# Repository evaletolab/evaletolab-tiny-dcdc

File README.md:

# Low cost, high efficiency, step-up DC-DC converter  
> [ input min 0.7V or 0.85V - output 3V, 3.3V or 5V - boost efficiency max 95% ]

This is an easy and tiny way to manage variable and small input voltage with your MCU project.
Using the [LTC3525](http://www.linear.com/product/LTC3525) you always get constant output voltage whatever your input voltage. Even at 1.2V as input the step-up keep >85% of the energy.

* **Up to 95% Efficiency**
* **Ultra small case 6x11mm**
* External solar panel input **with diode protection**
* Input startup voltage at 0.7V or 0.85V
* Plug external small battery or a super capacitor
* Output Disconnect and Inrush Current Limit
* Fixed Output Voltages of 3V, 3.3V or 5V
* Delivers 65mA at 3V from a 1V Input
* Delivers 60mA at 3.3V from a 1V Input, or 140mA at 3.3V from a 1.8V Input
* Delivers 175mA at 5V from a 3V Input
* <1μA Shutdown Current

<!--  -->

# The PCB

**THIS IS ALPHA SOFTWARE/HARDWARE AND SHOULD BE TREATED ACCORDINGLY.**
**IT IS FUN TO GET RUNNING, BUT EXPECT THINGS TO BE BROKEN.**
 
## License
GPL3
> Copyright (c) 2012 Olivier Evalet (http://evaletolab.ch/)

Permission is hereby granted, free of charge, to any person obtaining a copy
of this software and associated documentation files (the “Software”), to deal
in the Software without restriction, including without limitation the rights
to use, copy, modify, merge, publish, distribute, sublicense, and/or sell
copies of the Software, and to permit persons to whom the Software is
furnished to do so, subject to the following conditions:

The above copyright notice and this permission notice shall be included in
all copies or substantial portions of the Software.

THE SOFTWARE IS PROVIDED “AS IS”, WITHOUT WARRANTY OF ANY KIND, EXPRESS OR
IMPLIED, INCLUDING BUT NOT LIMITED TO THE WARRANTIES OF MERCHANTABILITY,
FITNESS FOR A PARTICULAR PURPOSE AND NONINFRINGEMENT. IN NO EVENT SHALL THE
AUTHORS OR COPYRIGHT HOLDERS BE LIABLE FOR ANY CLAIM, DAMAGES OR OTHER
LIABILITY, WHETHER IN AN ACTION OF CONTRACT, TORT OR OTHERWISE, ARISING FROM,
OUT OF OR IN CONNECTION WITH THE SOFTWARE OR THE USE OR OTHER DEALINGS IN
THE SOFTWARE.

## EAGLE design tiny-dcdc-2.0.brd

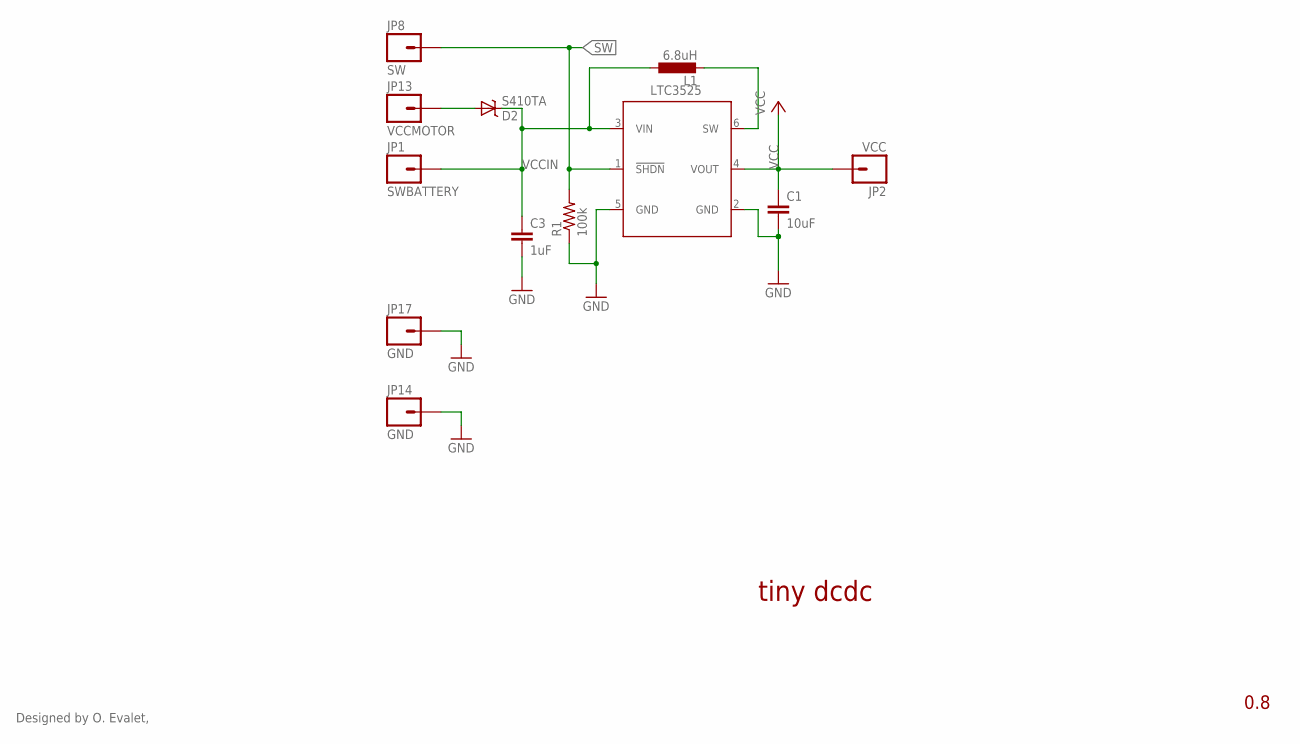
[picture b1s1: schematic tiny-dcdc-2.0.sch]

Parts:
C1: 10uF; 0805
C3: 1uF; 0805
D2: S410TA; SOD-323
JP1: SWBATTERY; URWERK1X01
JP2: VCC; URWERK1X01
JP8: SW; URWERK1X01
JP13: VCCMOTOR; URWERK1X01
JP14, JP17: GND; URWERK1X01
L1: 6.8uH; L2012C
R1: 100k; 0805
U$3: LTC3525; SC70-6L

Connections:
GND: C1.2, C3.2, JP14.1, JP17.1, R1.1, U$3.2 (GND), U$3.5 (GND)
unnamed: L1.2, U$3.6 (SW)
SW: JP8.1, R1.2, U$3.1 (!SHDN)
VCC: C1.1, JP2.1, U$3.4 (VOUT)
VCCIN: C3.1, D2.1 (C), JP1.1, L1.1, U$3.3 (VIN)
VCCMOTOR: D2.2 (A), JP13.1

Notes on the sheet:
0.8
tiny dcdc
Designed by O. Evalet,

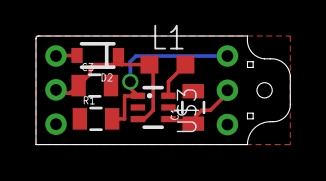
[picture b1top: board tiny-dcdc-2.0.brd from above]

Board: 2 copper layers, 14.1 x 6.0 mm, 12 parts (0 on the bottom side), 6 nets.

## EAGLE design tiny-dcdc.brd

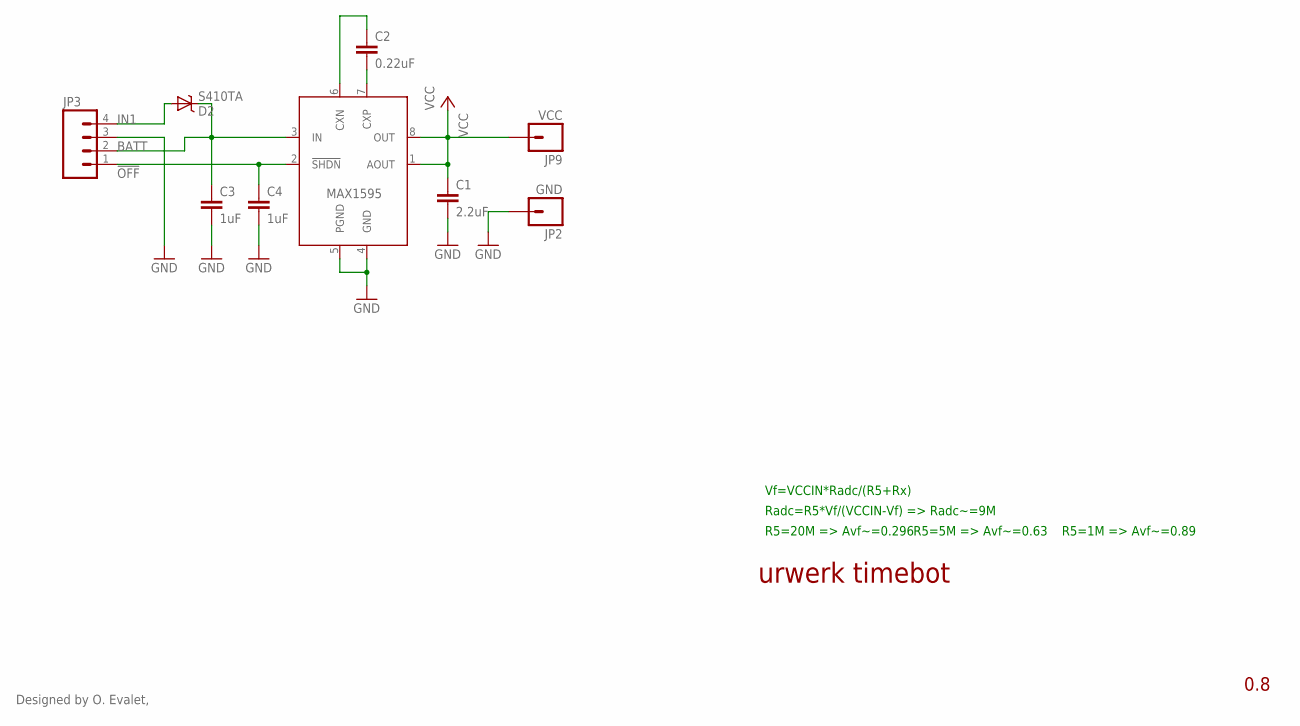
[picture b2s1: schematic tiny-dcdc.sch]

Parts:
C1: 2.2uF; 0805
C2: 0.22uF; 0805
C3, C4: 1uF; 0805
D2: S410TA; SOD-323
JP2: GND; URWERK1X01
JP3: M041.27MM; 1X04-1.27MM
JP9: VCC; URWERK1-SMALLX01
U$1: MAX1595; UMAX8

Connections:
!OFF: C4.1, JP3.1, U$1.2 (!SHDN)
BATT: C3.1, D2.1 (C), JP3.2, U$1.3 (IN)
GND: C1.2, C3.2, C4.2, JP2.1, JP3.3, U$1.4 (GND), U$1.5 (PGND)
IN1: D2.2 (A), JP3.4
unnamed: C2.2, U$1.7 (CXP)
unnamed: C2.1, U$1.6 (CXN)
VCC: C1.1, JP9.1, U$1.1 (AOUT), U$1.8 (OUT)

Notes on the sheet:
0.8
urwerk timebot
Designed by O. Evalet,
Vf=VCCIN*Radc/(R5+Rx)
Radc=R5*Vf/(VCCIN-Vf) => Radc~=9M
R5=5M => Avf~=0.63
R5=1M => Avf~=0.89
R5=20M => Avf~=0.296

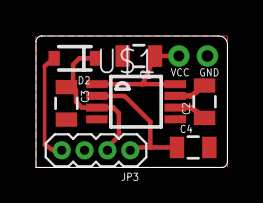
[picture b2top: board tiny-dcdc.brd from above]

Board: 2 copper layers, 10.6 x 7.3 mm, 9 parts (0 on the bottom side), 7 nets.

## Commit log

2015-06-27 initial release
